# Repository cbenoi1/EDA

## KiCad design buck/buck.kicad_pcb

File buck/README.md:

This is a simple buck converter. Kicad 6.0. Ready for JLCPCB.

Datasheet: https://datasheet.lcsc.com/lcsc/2201241030_TECH-PUBLIC-TPMP2359DJ_C2959845.pdf

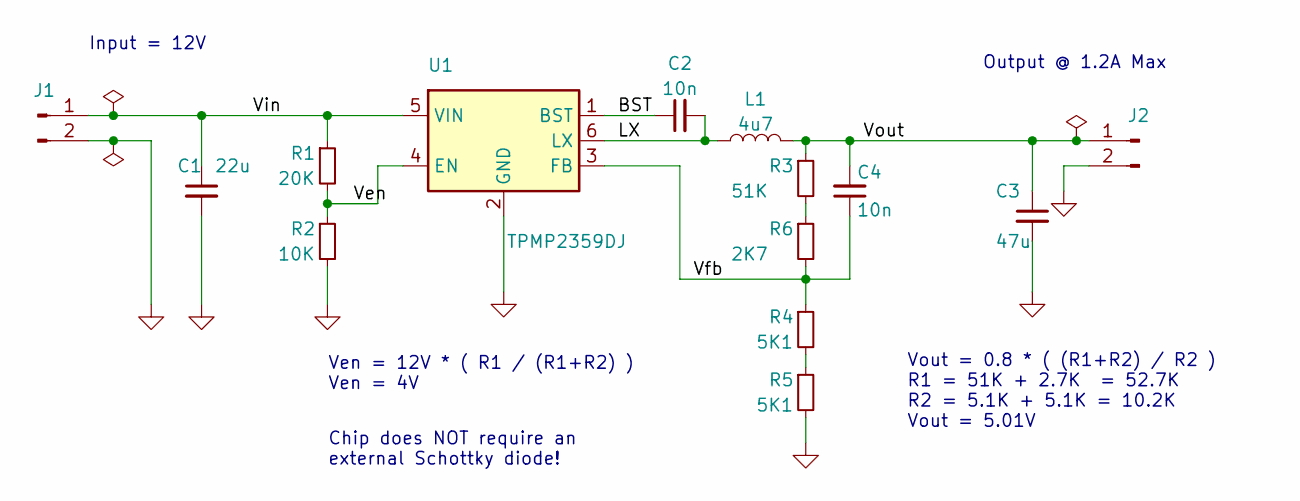
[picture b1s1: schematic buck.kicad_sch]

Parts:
C1: 22u; C_0805_2012Metric; JLCPCB Part # C32375
C2, C4: 10n; C_0402_1005Metric; JLCPCB Part # C15195
C3: 47u; C_1206_3216Metric; JLCPCB Part # C96123
J1, J2: Conn_01x02_Male; PinSocket_1x02_P2.54mm_Vertical
L1: 4u7; L_0805_2012Metric_Pad1.15x1.40mm_HandSolder; JLCPCB Part # C383376
R1: 20K; R_0402_1005Metric; JLCPCB Part # C25750
R2: 10K; R_0402_1005Metric; JLCPCB Part # C11616
R3: 51K; R_0402_1005Metric; JLCPCB Part # C25794
R4, R5: 5K1; R_0402_1005Metric; JLCPCB Part # C25905
R6: 2K7; R_0402_1005Metric; JLCPCB Part # C140189
U1: TPMP2359DJ; SOT-23-6; JLCPCB Part # C2959845

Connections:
/BST: C2.1, U1.1 (BST)
/LX: C2.2, L1.1, U1.6 (LX)
/Ven: R1.2, R2.1, U1.4 (EN)
/Vfb: C4.1, R4.1, R6.2, U1.3 (FB)
/Vin: C1.1, J1.1, R1.1, U1.5 (VIN)
/Vout: C3.1, C4.2, J2.1, L1.2, R3.1
GND: C1.2, C3.2, J1.2, J2.2, R2.2, R5.2, U1.2 (GND)
unnamed: R3.2, R6.1
unnamed: R4.2, R5.1

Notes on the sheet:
Vout = 0.8 * ( (R1+R2) / R2 ) R1 = 51K + 2.7K = 52.7K R2 = 5.1K + 5.1K = 10.2K Vout = 5.01V
Ven = 12V * ( R1 / (R1+R2) ) Ven = 4V
Chip does NOT require an external Schottky diode!
Output @ 1.2A Max
Input = 12V

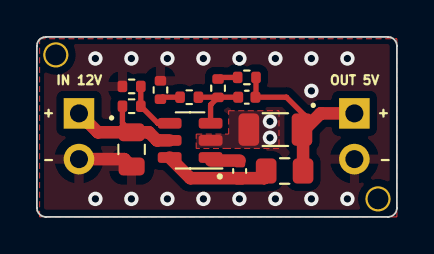
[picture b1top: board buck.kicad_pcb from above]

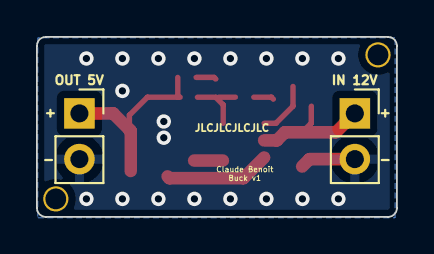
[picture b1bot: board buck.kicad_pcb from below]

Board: 2 copper layers, 20.0 x 10.0 mm, 14 parts (2 on the bottom side), 9 nets.

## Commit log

2022-12-17 first check-in
2022-12-17 check-in
2022-12-17 added images
2022-12-20 update for JLCPCB
